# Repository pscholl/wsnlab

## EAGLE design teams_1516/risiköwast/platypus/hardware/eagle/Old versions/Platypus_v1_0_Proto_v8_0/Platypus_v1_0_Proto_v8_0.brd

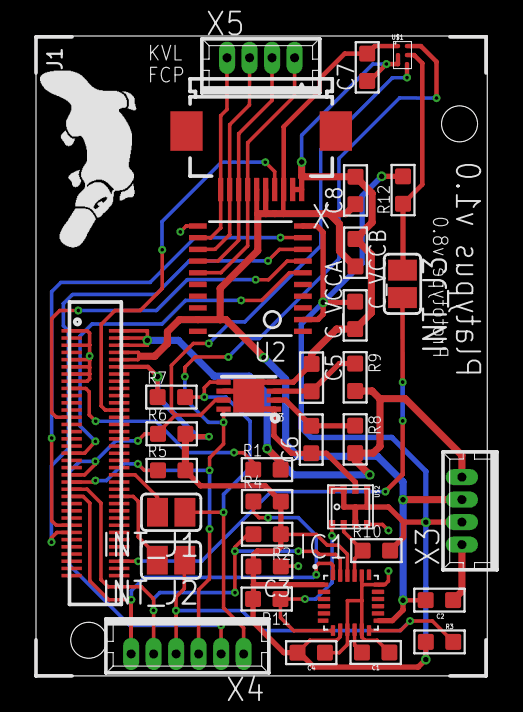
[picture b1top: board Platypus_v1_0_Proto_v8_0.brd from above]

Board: 2 copper layers, 25.1 x 35.5 mm, 35 parts (0 on the bottom side), 29 nets.

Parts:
C1, C7: 0.1µF; C0603
C2, C3: 100nF; C0603
C4, C5: 10nF; C0603
C6, C8: 1µF; C0603
C_VCCA: 0.1µF; C0603
C_VCCB: 0.1µF; C0603
IC1: MPU-9250; QFN24-SMALL
INT_J1, INT_J2, INT_J3: SJ
J1: EDISON_CONNECTOR_FULLMOUNTING_HOLES; EDISON_DAUGHTER
R1, R2, R3, R4: 10k; R0603
R5, R6, R7, R10, R11, R12: 4.7k; R0603
R8: 1k; R0603
R9: 150; R0603
U2: TXS0108E; TSSOP20
U3: MAX17043; TDFN-8
U$1: TSL2584TSV6-XFBGA; 6-XFBGA
U$2: BME280LGA-8; LGA-8
X: SHARP96; FH12-10S-0.5SH
X3: Power TP; 53047-04
X4: I2C TP; 53047-06
X5: Display TP; 53047-04

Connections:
1.8V: C3.2, C4.2, C_VCCA.2, IC1.1, IC1.8, IC1.22, J1.12, R2.1, R3.2, R4.2, R5.2, R6.2, R7.1, R10.2, R11.2, R12.2, U2.2, U2.10, U$2.P$2, U$2.P$5, U$2.P$6, U$2.P$8, X3.3
3.3V: C2.2, C7.2, C8.1, C_VCCB.2, IC1.13, J1.8, J1.10, U2.19, U$1.P$1, X.3, X.5, X.6, X3.2
ALS_INT: INT_J3.1, R12.1, U$1.P$5
AUX_CL: IC1.7, R11.1, U$2.P$4
AUX_DA: IC1.21, R10.1, U$2.P$3
BAT_ALERT: INT_J1.1, R7.2, U3.5, X4.6
GND: C1.1, C2.1, C3.1, C4.1, C5.1, C6.1, C7.1, C8.2, C_VCCA.1, C_VCCB.1, IC1.9, IC1.11, IC1.18, IC1.20, J1.1, J1.5, J1.9, J1.11, J1.13, J1.15, U2.11, U3.1, U3.4, U3.6, U3.EP, U$1.P$2, U$1.P$3, U$2.P$1, U$2.P$7, X.1, X.2, X3.4
GP12_PWM0: J1.35, U2.6
GP14: INT_J2.2, J1.48
GP15: INT_J1.2, J1.42
GP19_I2C_1_SCL: J1.41, R6.1, U3.7, U$1.P$4, X4.5
GP20_I2C_1_SDA: J1.43, R5.1, U3.8, U$1.P$6, X4.4
GP27_I2C_6_SCL: IC1.23, J1.45, R2.2, X4.2
GP28_I2C_6_SDA: IC1.24, J1.47, R4.1, X4.1
GP44: J1.24, X.4
GP80_SD_0_DAT0: INT_J3.2, J1.66
GP109_SPI_2_CLK: J1.55, U2.9
GP115_SPI_2_TXD: J1.57, U2.8
GP165: J1.25, U2.7
IMU_INT: IC1.12, INT_J2.1, R3.1, X4.3
unnamed: C1.2, IC1.10
unnamed: C6.2, R8.1, U3.2
unnamed: C5.2, R9.1, U3.3
PWRBTN#: J1.17, R1.1
SHARP_EXT: U2.15, X.7, X5.1
SHARP_SCLK: U2.12, X.10, X5.4
SHARP_SCS: U2.14, X.8, X5.2
SHARP_SI: U2.13, X.9, X5.3
VSYS: J1.2, J1.4, J1.6, R1.2, R8.2, R9.2, X3.1

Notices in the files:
parts and their libraries:
SparkFun-PowerIC: Licensing: Creative Commons ShareAlike 4.0 International - https://creativecommons.org/licenses/by-sa/4.0
